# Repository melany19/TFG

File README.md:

# TFG: Desarrollo de un prototipo de herramientas electrónicas para mediciones eléctricas de bajo costo

El presente proyecto muestra el desarrollo completo de cuatro herramientas electrónicas básicas las cuales son: fuente de alimentación, generador de ondas, voltímetro y osciloscopio; estas herramientas son básicas con respecto a la toma de mediciones en los circuitos. El proyecto desarrollado muestra su diseño de circuito electrónico, circuito impreso y diseño de la carcasa como objeto 3D, de igual forma se muestran las pruebas para corroborar su buena funcionalidad.

Se explican de forma extensa los pasos a seguir con sus diagramas para su respectivo desarrollo, concluyendo con el producto final funcional de las cuatro herramientas mencionadas.

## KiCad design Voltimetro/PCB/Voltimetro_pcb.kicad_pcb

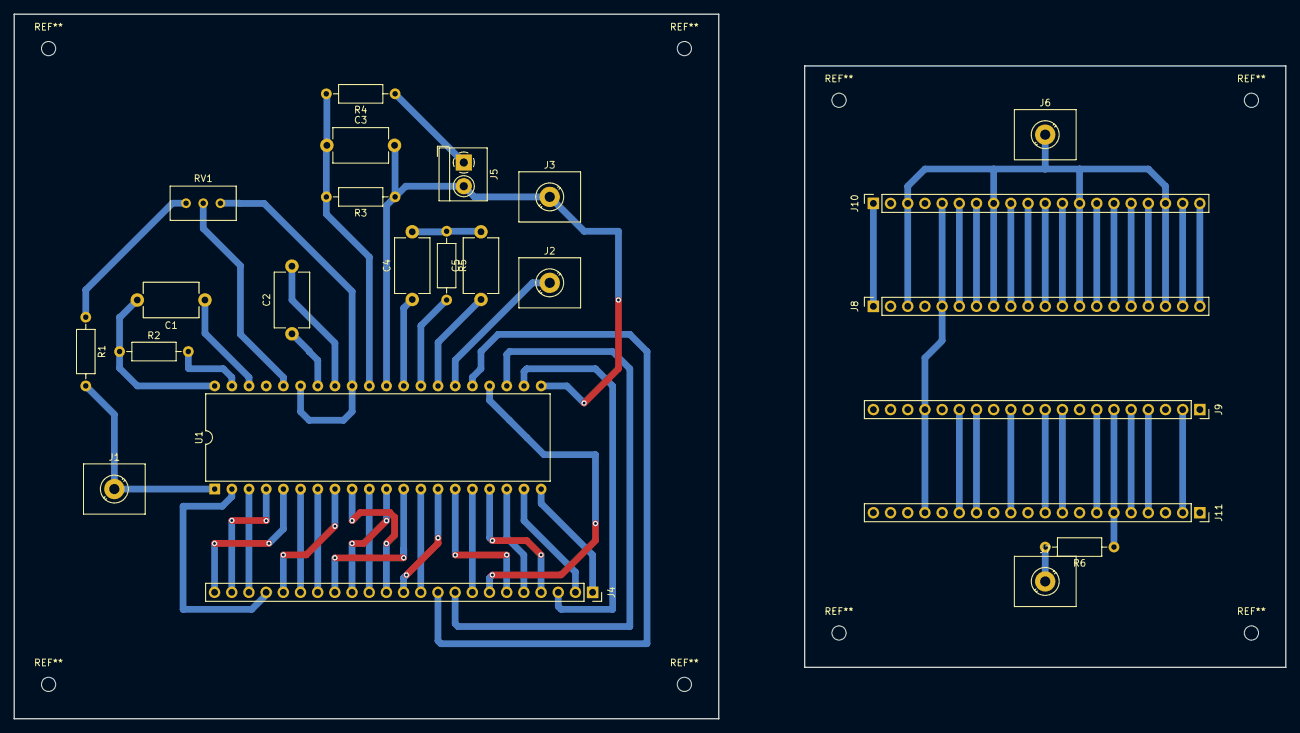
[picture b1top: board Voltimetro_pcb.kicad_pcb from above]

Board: 2 copper layers, 188.0 x 104.1 mm, 24 parts (0 on the bottom side), 41 nets.

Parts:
C1: 100p; C_Disc_D8.0mm_W5.0mm_P10.00mm
C2, C3: 100n; C_Disc_D8.0mm_W5.0mm_P10.00mm
C4: 470n; C_Disc_D8.0mm_W5.0mm_P10.00mm
C5: 220n; C_Disc_D8.0mm_W5.0mm_P10.00mm
J1, J2, J3, J6, J7: Conn_01x01; TerminalBlock_MetzConnect_360271_1x01_Horizontal_ScrewM3.0_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
J4: Conn_01x23; PinSocket_1x23_P2.54mm_Vertical
J5: Conn_01x02; TerminalBlock_4Ucon_1x02_P3.50mm_Horizontal
J8, J9, J10, J11: Conn_01x20; PinSocket_1x20_P2.54mm_Vertical
R1: 22k; R_Axial_DIN0207_L6.3mm_D2.5mm_P10.16mm_Horizontal
R2: 100k; R_Axial_DIN0207_L6.3mm_D2.5mm_P10.16mm_Horizontal
R3: 1.2k; R_Axial_DIN0207_L6.3mm_D2.5mm_P10.16mm_Horizontal
R4: 1M; R_Axial_DIN0207_L6.3mm_D2.5mm_P10.16mm_Horizontal
R5: 47k; R_Axial_DIN0207_L6.3mm_D2.5mm_P10.16mm_Horizontal
R6: 560; R_Axial_DIN0207_L6.3mm_D2.5mm_P10.16mm_Horizontal
RV1: 100k; Potentiometer_Bourns_3296W_Vertical
U1: ICL7107CPL; DIP-40_W15.24mm

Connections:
GND: C3.2, J3.1, J5.2, J7.1, R3.1, R6.2, U1.21 (BP/GND), U1.30 (IN_LO)
unnamed: C1.1, U1.38 (OSC3)
unnamed: C1.2, R2.1, U1.40 (OSC1)
unnamed: C2.1, U1.34 (CREF+)
unnamed: C2.2, U1.33 (CREF-)
unnamed: C3.1, R3.2, R4.2, U1.31 (IN_HI)
unnamed: C4.1, U1.29 (A-Z)
unnamed: C4.2, C5.2, R5.1
unnamed: C5.1, U1.27 (INT)
unnamed: J1.1, J6.1, J8.3, J8.8, J8.13, J8.18, J10.3, J10.8, J10.13, J10.18, R1.2, U1.1 (V+)
unnamed: J2.1, U1.26 (V-)
unnamed: J5.1, R4.1
unnamed: J4.1, J8.1, J10.1, U1.20 (POL)
unnamed: J4.2, J8.5, J9.17, J10.5, J11.17, U1.19 (AB4)
unnamed: J4.3, J8.6, J10.6, U1.22 (G3)
unnamed: J4.4, J8.7, J10.7, U1.17 (F3)
unnamed: J4.9, J8.9, J10.9, U1.23 (A3)
unnamed: J4.8, J8.10, J10.10, U1.16 (B3)
unnamed: J4.10, J8.11, J10.11, U1.25 (G2)
unnamed: J4.11, J8.12, J10.12, U1.13 (F2)
unnamed: J4.16, J8.14, J10.14, U1.12 (A2)
unnamed: J4.15, J8.15, J10.15, U1.11 (B2)
unnamed: J4.17, J8.16, J10.16, U1.7 (G1)
unnamed: J4.18, J8.17, J10.17, U1.6 (F1)
unnamed: J4.23, J8.19, J10.19, U1.5 (A1)
unnamed: J4.22, J8.20, J10.20, U1.4 (B1)
unnamed: J4.21, J9.2, J11.2, U1.3 (C1)
unnamed: J4.20, J9.4, J11.4, U1.2 (D1)
unnamed: J4.19, J9.5, J11.5, U1.8 (E1)
unnamed: J9.6, J11.6, R6.1
unnamed: J4.14, J9.7, J11.7, U1.10 (C2)
unnamed: J4.13, J9.9, J11.9, U1.9 (D2)
unnamed: J4.12, J9.10, J11.10, U1.14 (E2)
unnamed: J4.7, J9.12, J11.12, U1.24 (C3)
unnamed: J4.6, J9.14, J11.14, U1.15 (D3)
unnamed: J4.5, J9.15, J11.15, U1.18 (E3)
unnamed: R1.1, RV1.3
unnamed: R2.2, U1.39 (OSC2)
unnamed: R5.2, U1.28 (BUFF)
unnamed: RV1.1, U1.32 (COMMON), U1.35 (REF_LO)
unnamed: RV1.2, U1.36 (REF_HI)

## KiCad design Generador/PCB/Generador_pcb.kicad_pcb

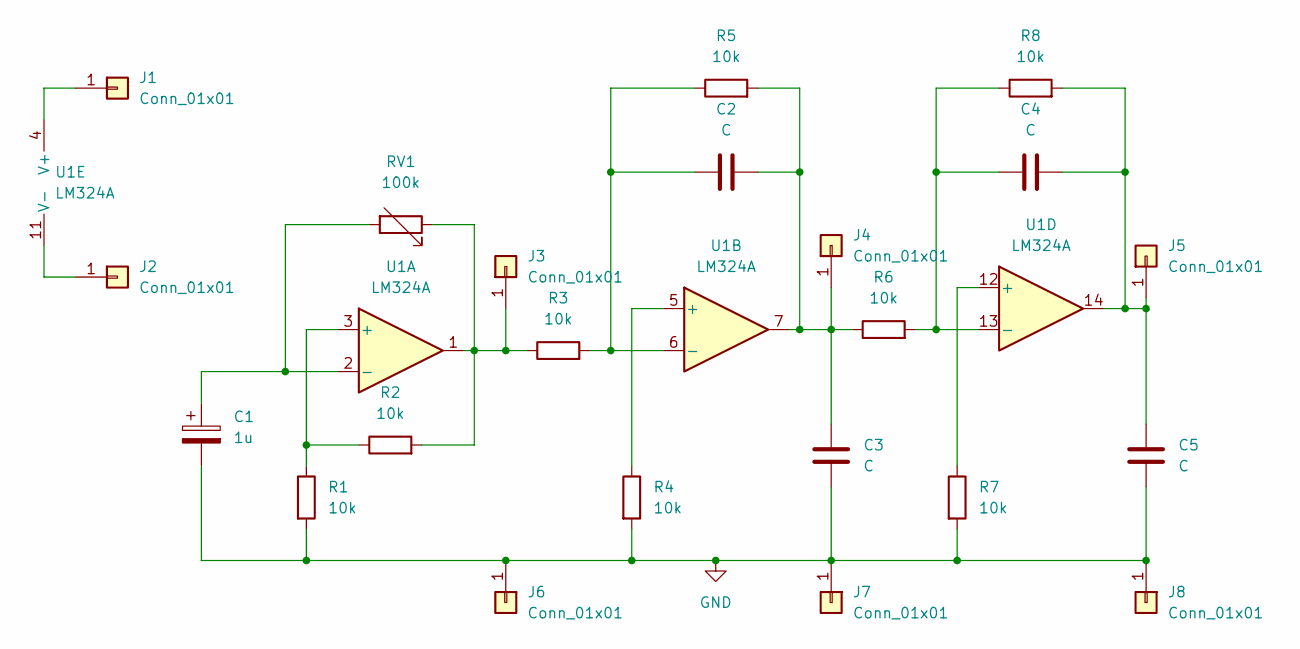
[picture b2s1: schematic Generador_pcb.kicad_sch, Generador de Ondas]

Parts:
C1: 1u; CP_Radial_D5.0mm_P2.50mm
C2, C4: C; C_Disc_D8.0mm_W5.0mm_P10.00mm
C3, C5: C; C_Rect_L4.6mm_W3.0mm_P2.50mm_MKS02_FKP02
J1, J2, J3, J4, J5, J6, J7, J8: Conn_01x01; TerminalBlock_MetzConnect_360271_1x01_Horizontal_ScrewM3.0_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
R1, R2, R3, R4, R5, R6, R7, R8: 10k; R_Axial_DIN0207_L6.3mm_D2.5mm_P10.16mm_Horizontal
RV1: 100k; Potentiometer_Alps_RK163_Single_Horizontal
U1: LM324A; DIP-14_W7.62mm_LongPads

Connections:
GND: C1.2, C3.1, C5.1, J6.1, J7.1, J8.1, R1.2, R4.2, R7.2
unnamed: C1.1, RV1.2, U1.2 (-)
unnamed: C2.1, R3.2, R5.1, U1.6 (-)
unnamed: C2.2, C3.2, J4.1, R5.2, R6.1, U1.7
unnamed: C4.1, R6.2, R8.1, U1.13 (-)
unnamed: C4.2, C5.2, J5.1, R8.2, U1.14
unnamed: J1.1, U1.4 (V+)
unnamed: J2.1, U1.11 (V-)
unnamed: J3.1, R2.2, R3.1, RV1.1, U1.1
unnamed: R1.1, R2.1, U1.3 (+)
unnamed: R4.1, U1.5 (+)
unnamed: R7.1, U1.12 (+)

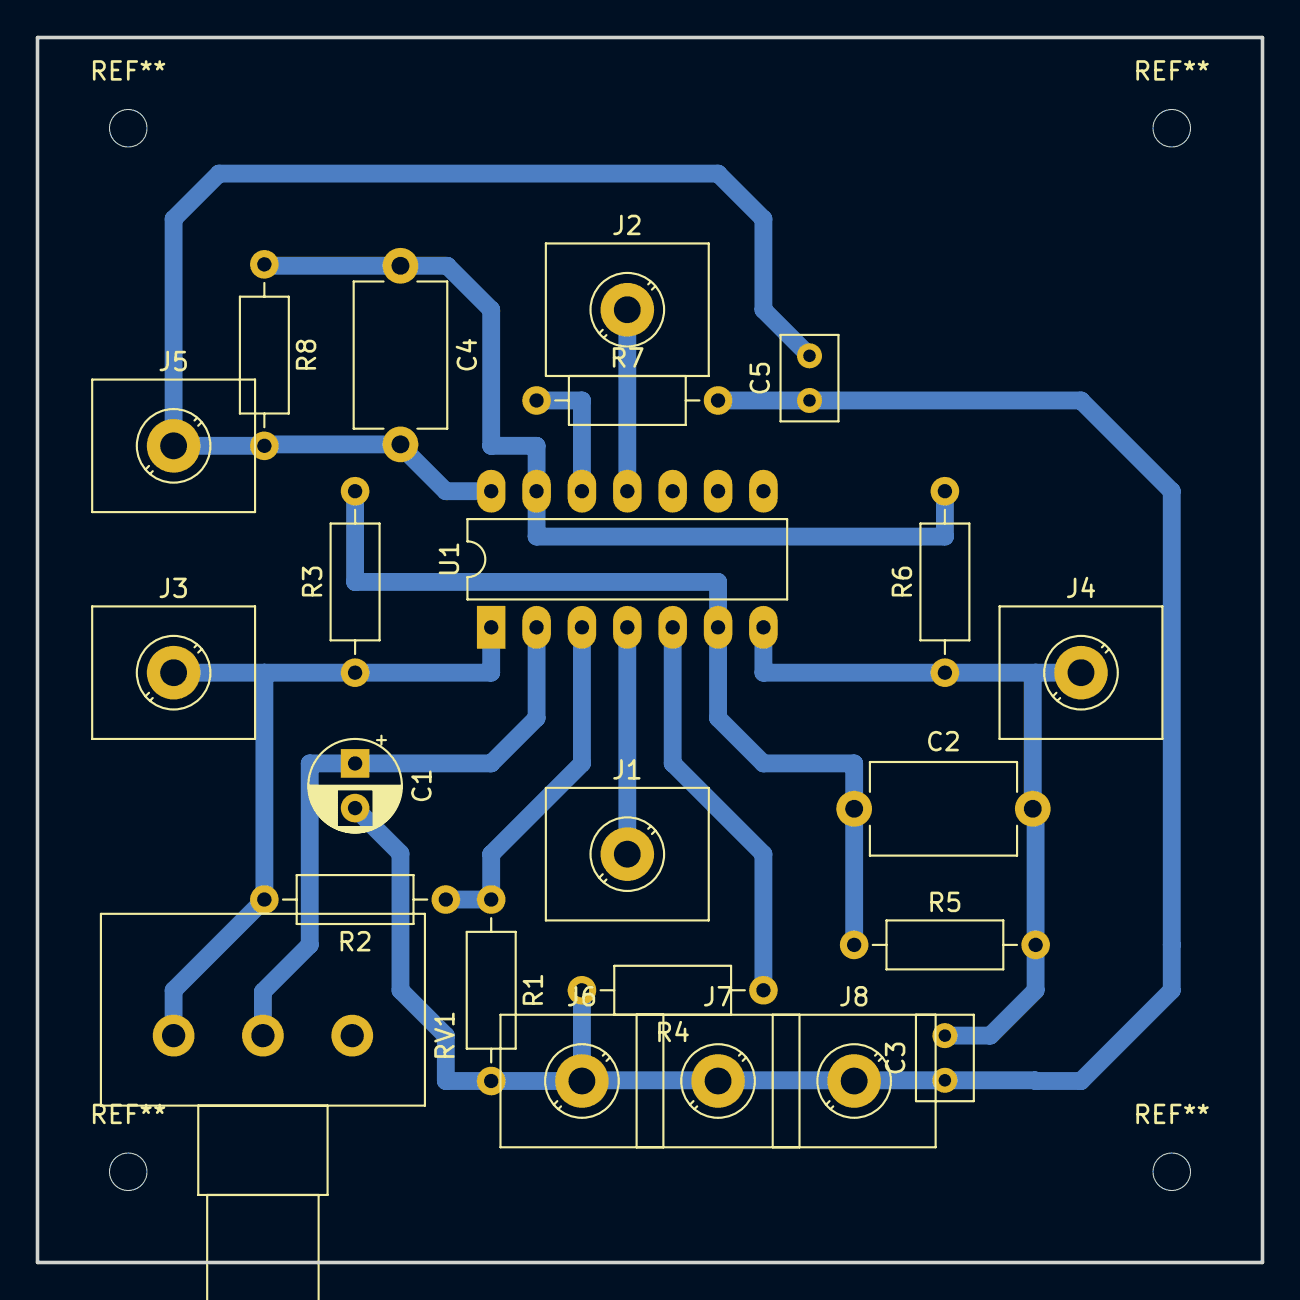
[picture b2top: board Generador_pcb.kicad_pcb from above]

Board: 2 copper layers, 68.6 x 68.6 mm, 23 parts (0 on the bottom side), 12 nets.

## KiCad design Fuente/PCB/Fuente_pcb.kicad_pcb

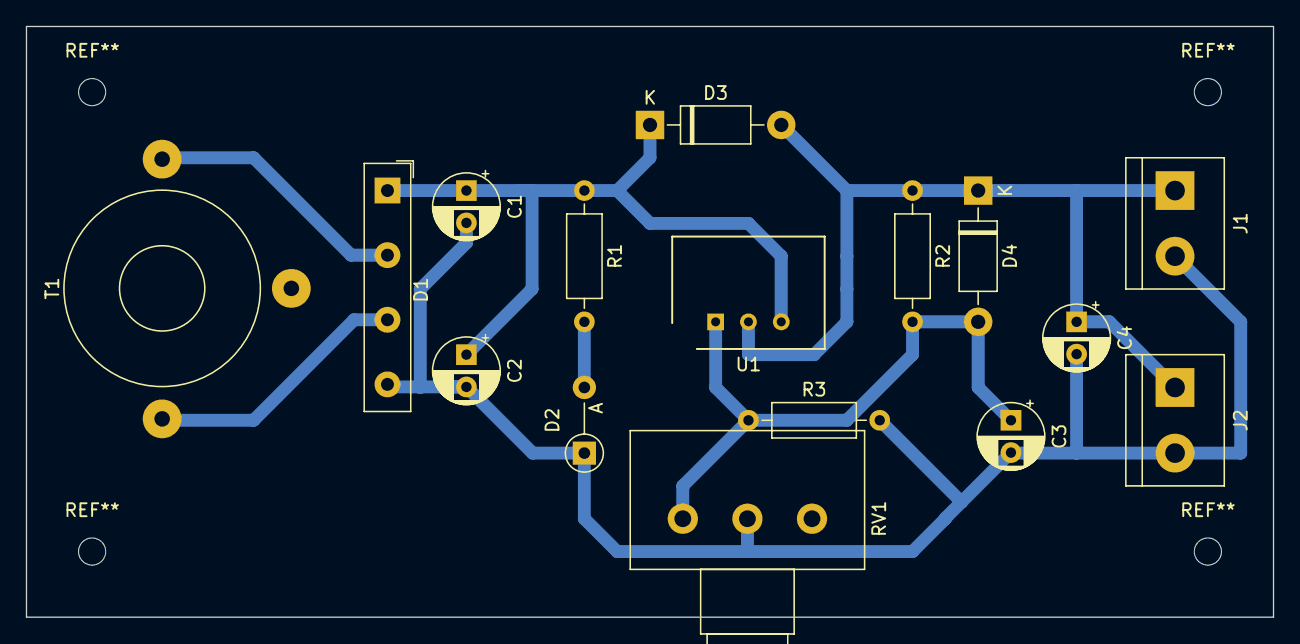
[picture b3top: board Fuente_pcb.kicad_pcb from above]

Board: 2 copper layers, 96.5 x 45.7 mm, 16 parts (0 on the bottom side), 6 nets.

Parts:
C1, C2: 2200u; CP_Radial_D5.0mm_P2.50mm
C3: 33u; CP_Radial_D5.0mm_P2.50mm
C4: 1u; CP_Radial_D5.0mm_P2.50mm
D1: D_Bridge_+AA-; Diode_Bridge_19.0x3.5x10.0mm_P5.0mm
D2: LED; D_A-405_P5.08mm_Vertical_AnodeUp
D3, D4: 1N5817; D_DO-41_SOD81_P10.16mm_Horizontal
J1, J2: Conn_01x02; TerminalBlock_bornier-2_P5.08mm
R1: 1k; R_Axial_DIN0207_L6.3mm_D2.5mm_P10.16mm_Horizontal
R2: 220; R_Axial_DIN0207_L6.3mm_D2.5mm_P10.16mm_Horizontal
R3: 20k; R_Axial_DIN0207_L6.3mm_D2.5mm_P10.16mm_Horizontal
RV1: 5k; Potentiometer_Alps_RK163_Single_Horizontal
T1: Transformer_1P_SS; Autotransformer_Toroid_1Tap_Horizontal_D14.0mm_Amidon-T50
U1: LM350_TO220; SIP3_11.6x8.5mm

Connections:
GND: C1.2, C2.2, C3.2, C4.2, D1.4 (-), D2.1 (K), J1.2, J2.2, R3.2, RV1.2
unnamed: C1.1, C2.1, D1.1 (+), D3.1 (K), R1.1, U1.3 (VI)
unnamed: C3.1, D4.2 (A), R2.2, R3.1, RV1.1, U1.1 (ADJ)
unnamed: C4.1, D3.2 (A), D4.1 (K), J1.1, J2.1, R2.1, U1.2 (VO)
unnamed: D1.2, T1.3 (SA)
unnamed: D2.2 (A), R1.2

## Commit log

2023-01-23 Herramientas electrónicas
2023-04-17 Proyecto finalizado
